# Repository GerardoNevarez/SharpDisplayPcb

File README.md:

# SharpDisplayPcb

Replacement PCB for the Adafruit SHARP Memory Display Breakout (3502). Only for 3.3V.

Documentation - WIP

BOM ( Bill Of Materials )
- PCB 😄

| Ref | Qty | Value  | Description                       | Package | Manufacturer_Part | Mouser_Part          | 
------------|----------|--------|-----------------------------------|---------|-------------------|----------------------|
| FB1, FB2  |    2     |   FB   |  Ferrite Beads 0805               | 0805    | 2508051217Z3      | 623-2508051217Z3     |
| C1        |    1     |  10uF  | Ceramic Capacitors 10uF+/-10% 16V | 0805    |  CL21A106KOQNNNG  |  187-CL21A106KOQNNNG |
| C2        |    1     | 0.1uF  | Ceramic Capacitors 100nF+/-10% 50V  | 0805    |  CL21B104KBCNNNC   |  187-CL21B104KBCNNNC  |
| C3, C4    |    2     |  1uF   | Ceramic Capacitors 1uF+/-10% 16V  | 0805    |  CL21B105KOFNNNF  |  187-CL21B105KOFNNNF |
| R1        |    1     |  5.1K   | Thick Film Resistors - SMD 5.1 kOhms 125 mW 1%   | 0805    |  RC0805FR-075K1L   |  603-RC0805FR-075K1L  |
| J2        |    1     |  ZIF   | FFC & FPC Connectors 0.5mmpitch 10Ckt | 10 pin FPC    |  505278-1033   |  538-505278-1033  |

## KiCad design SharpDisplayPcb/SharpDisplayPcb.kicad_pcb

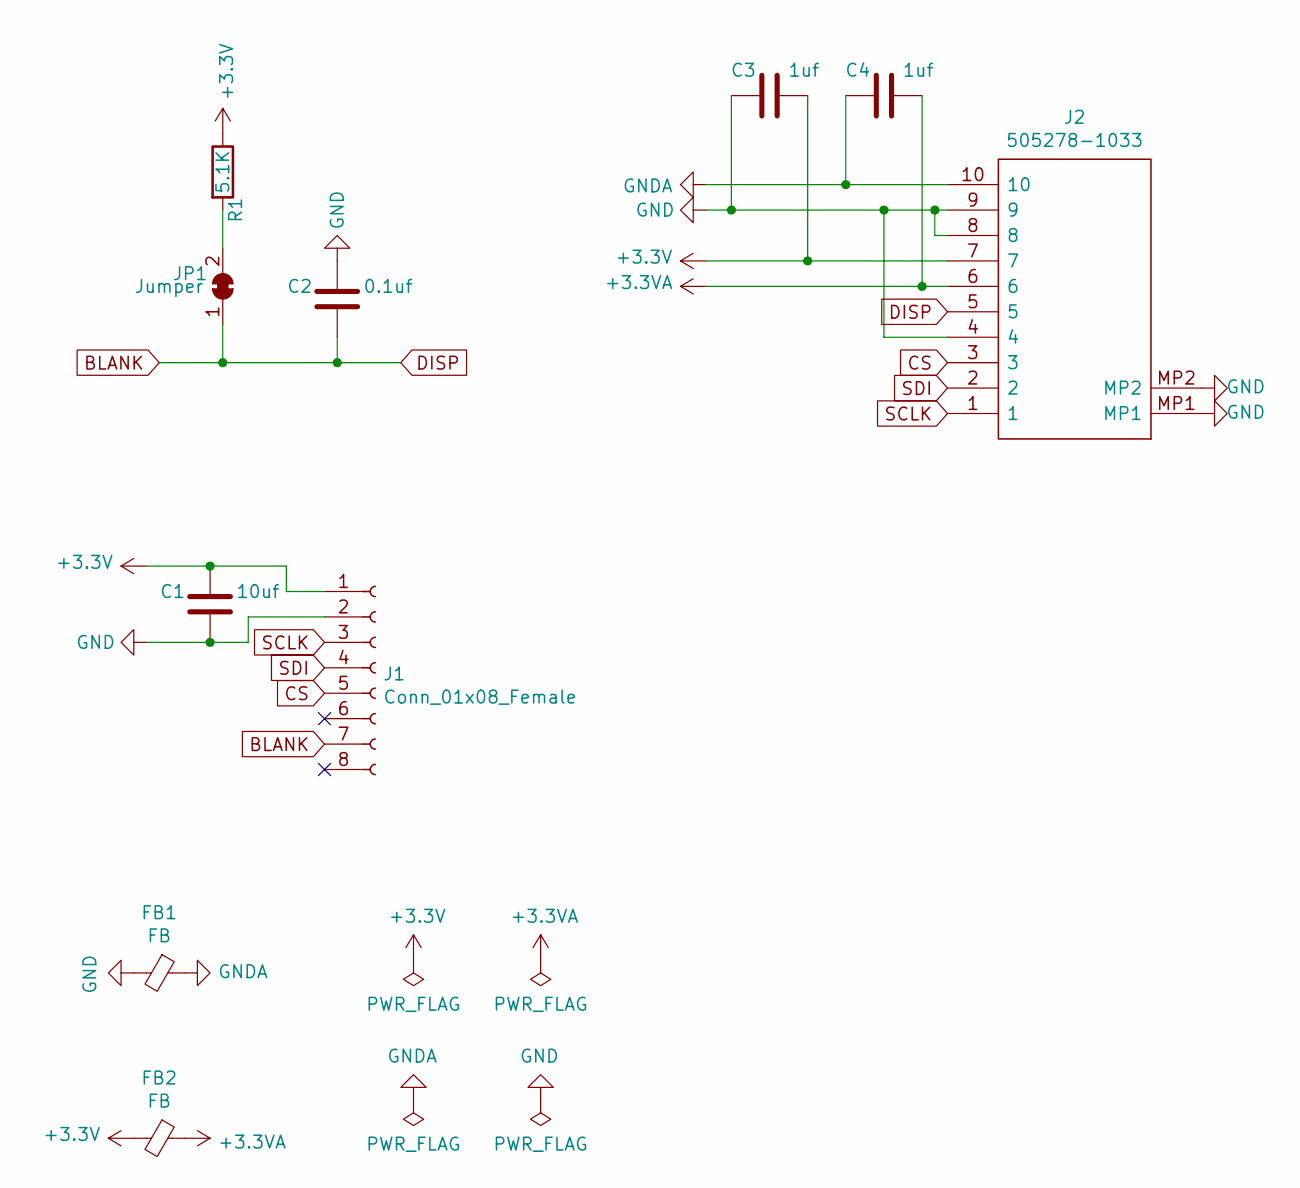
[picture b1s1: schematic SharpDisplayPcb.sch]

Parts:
C1: 10uf; C_0805_2012Metric_Pad1.18x1.45mm_HandSolder
C2: 0.1uf; C_0805_2012Metric_Pad1.18x1.45mm_HandSolder
C3, C4: 1uf; C_0805_2012Metric_Pad1.18x1.45mm_HandSolder
FB1, FB2: FB; L_0805_2012Metric_Pad1.15x1.40mm_HandSolder
J1: Conn_01x08_Female; PinHeader_1x08_P2.54mm_Vertical
J2: 505278-1033; 5052781033; Mouser Part Number 538-505278-1033
JP1: Jumper; SolderJumper-2_P1.3mm_Bridged_Pad1.0x1.5mm
R1: 5.1K; R_0805_2012Metric_Pad1.20x1.40mm_HandSolder

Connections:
+3.3VA: C4.2, FB2.1, J2.6
+3V3: C1.1, C3.2, FB2.2, J1.1, J2.7, R1.1
BLANK: C2.2, J1.7, J2.5, JP1.1 (A)
CS: J1.5, J2.3
GND: C1.2, C2.1, C3.1, FB1.2, J1.2, J2.4, J2.8, J2.9, J2.MP1, J2.MP2
GNDA: C4.1, FB1.1, J2.10
unnamed: JP1.2 (B), R1.2
SCLK: J1.3, J2.1
SDI: J1.4, J2.2

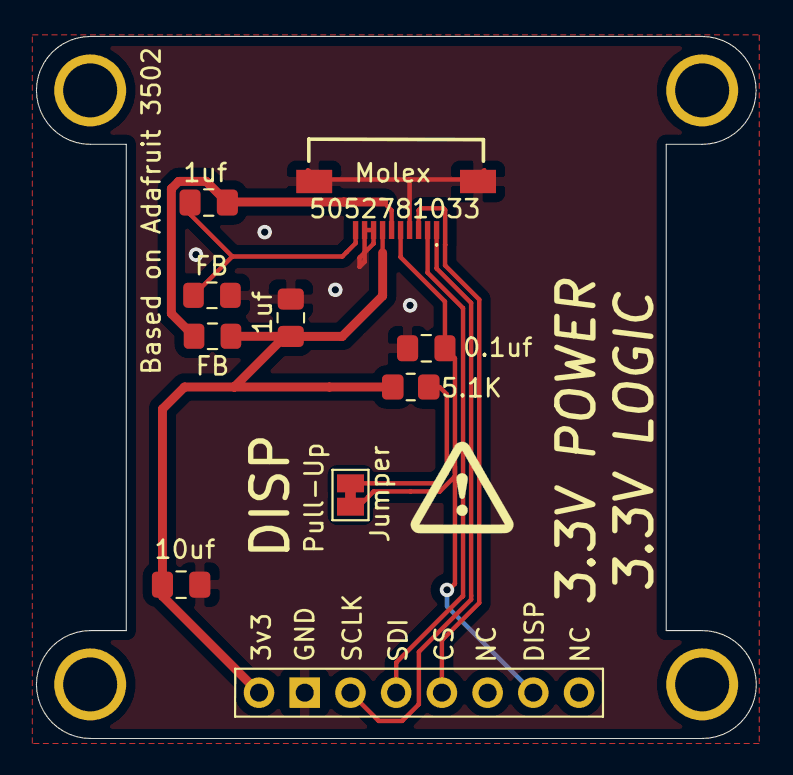
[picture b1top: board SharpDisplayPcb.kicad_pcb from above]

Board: 2 copper layers, 40.0 x 39.0 mm, 14 parts (0 on the bottom side), 9 nets.

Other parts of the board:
M3, M3#2, M3#3, M3#4: MH3; MountingHole_3mm_Pad

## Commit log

2021-09-07 Add Adafruit files, for reference
2021-09-07 PCB border, start schematic
2021-09-08 Completed schematics, initial PCB layout
2021-10-19 Better routing for 3v3 bypass capacitor
2021-10-19 Added notes with ZIF connector drama
2021-10-19 Add DISP jumper, to disable pull-up resistor
2021-10-19 Remove pull-down resistors, adjust layout
2021-10-19 Replace ZIF part, move components out of ZIF footprint
2021-10-27 Create LICENSE
